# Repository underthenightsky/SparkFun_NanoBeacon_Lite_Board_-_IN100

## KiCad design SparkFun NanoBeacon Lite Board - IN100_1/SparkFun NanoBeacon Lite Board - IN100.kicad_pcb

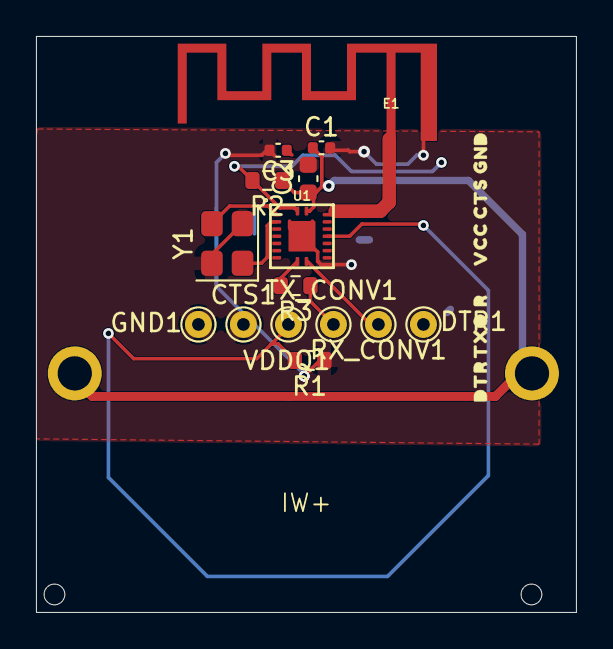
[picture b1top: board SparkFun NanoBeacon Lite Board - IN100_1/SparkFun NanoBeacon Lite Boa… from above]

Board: 2 copper layers, 30.0 x 32.0 mm, 16 parts (1 on the bottom side), 9 nets.

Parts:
BT1: Battery_Cell; BatteryHolder_Keystone_3009_1x2450
C1, C3: 0.1uF; C_0402_1005Metric
C2: 10uF; C_0603_1608Metric
CTS1: TestPoint; TestPoint_THTPad_D1.5mm_Drill0.7mm
DTR1: TestPoint; TestPoint_THTPad_D1.5mm_Drill0.7mm
E1: ANTENNA-GROUNDEDTRACE-15.2MM; TRACE_ANTENNA_2.4GHZ_15.2MM
GND1: TestPoint; TestPoint_THTPad_D1.5mm_Drill0.7mm
R1: 10k; R_0603_1608Metric
R2, R3: 1k; R_0603_1608Metric
RX_CONV1: TestPoint; TestPoint_THTPad_D1.5mm_Drill0.7mm
TX_CONV1: TestPoint; TestPoint_THTPad_D1.5mm_Drill0.7mm
U1: IN100
VDDQ1: TestPoint; TestPoint_THTPad_D1.5mm_Drill0.7mm
Y1: CRYSTAL-26MHZSMD-3.2X2.5; Crystal_SMD_3225-4Pin_3.2x2.5mm

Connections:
EN: C3.1, R2.2, U1.18 (EN)
GND: BT1.2 (-), C1.2, C2.2, C3.2, CTS1.1 (1_1), GND1.1 (1_1), R1.1, U1.19 (GND), Y1.2 (GND), Y1.4 (GND)
unnamed: R3.1, TX_CONV1.1 (1_1)
unnamed: R1.2, U1.13 (VDDQ), VDDQ1.1 (1_1)
unnamed: U1.1 (XO_N), Y1.3 (2)
unnamed: U1.2 (XO_P), Y1.1
RX/IO0: R3.2, U1.8 (RX/GPIO0)
TX/IO1: RX_CONV1.1 (1_1), U1.9 (TX/GPIO1)
VCC: BT1.1 (+), C1.1, C2.1, R2.1, U1.17 (VCC)

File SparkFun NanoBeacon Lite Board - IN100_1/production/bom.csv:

Designator,Footprint,Quantity,Value,LCSC Part #
BT1,BatteryHolder_Keystone_3009_1x2450,1,Battery_Cell,
"C1, C3",0402,2,0.1uF,
C2,0603,1,10uF,
"CTS1, DTR1, GND1, RX_CONV1, TX_CONV1, VDDQ1",TestPoint_THTPad_D1.5mm_Drill0.7mm,6,TestPoint,
E1,TRACE_ANTENNA_2.4GHZ_15.2MM,1,ANTENNA-GROUNDEDTRACE-15.2MM,
R1,0603,1,10k,
"R2, R3",0603,2,1k,
U1,IN100,1,IN100,
Y1,Crystal_SMD_3225-4Pin_3.2x2.5mm,1,CRYSTAL-26MHZSMD-3.2X2.5,

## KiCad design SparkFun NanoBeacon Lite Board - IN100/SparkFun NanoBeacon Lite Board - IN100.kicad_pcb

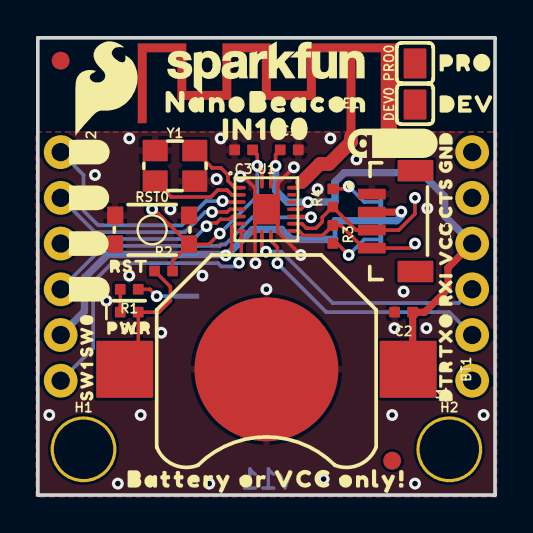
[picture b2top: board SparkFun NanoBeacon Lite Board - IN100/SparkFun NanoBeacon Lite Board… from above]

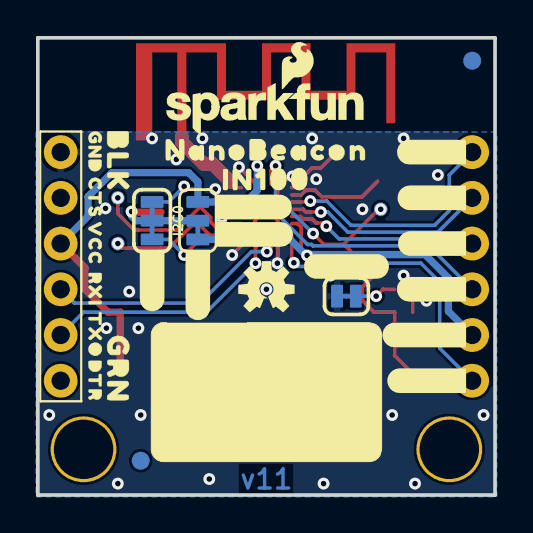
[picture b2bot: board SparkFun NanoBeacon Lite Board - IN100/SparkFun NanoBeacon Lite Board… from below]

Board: 2 copper layers, 25.4 x 25.4 mm, 63 parts (24 on the bottom side), 21 nets.

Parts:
BT1: BATTCON_12MM
BUS0: JUMPER-SMT_3_1-NC_TRACE_SILK; SMT-JUMPER_3_1-NC_TRACE_SILK
C1, C3: 0.1uF; 0402-TIGHT
C2: 10uF; 0402-TIGHT
D1: RED; LED-0402
DEV0: PROD_ID_PASTE_SILK; PRODUCT_IDENT_PASTE_SILK
E1: ANTENNA-GROUNDEDTRACE-15.2MM; TRACE_ANTENNA_2.4GHZ_15.2MM
FD1, FD2, FD3, FD4: FIDUCIAL1X2; FIDUCIAL-1X2
FRAME1: FRAME-LETTER; CREATIVE_COMMONS
H1, H2: STAND-OFF
I2C0: JUMPER-SMT_3_2-NC_TRACE_SILK; SMT-JUMPER_3_2-NC_TRACE_SILK
J1, J2: 1X06_NO_SILK
J3: Vertical Qwiic Connector; JST04_1MM_VERT
LOGO1: OSHW-LOGOS; OSHW-LOGO-S
LOGO2: SFE_LOGO_NAME_FLAME.1_INCH; SFE_LOGO_NAME_FLAME_.1
LOGO3: QWIIC_LOGO_5MM; QWIIC_5MM
PRO0: PROD_ID_PASTE_SILK; PRODUCT_IDENT_PASTE_SILK
PWR0: JUMPER-SMT_2_NC_TRACE_SILK; SMT-JUMPER_2_NC_TRACE_SILK
R1, R3, R4: 2.2k; 0402-TIGHT
R2: 1k; 0402-TIGHT
RST0: MOMENTARY-SWITCH-SPST-SMD-4.6X2.8MM; TACTILE_SWITCH_SMD_4.6X2.8MM
TP1, TP2, TP3: TEST-POINT3; PAD.03X.03
U1: IN100
U$1, U$29: NANOBEACON0
U$2: #_7#0
U$3: #_6#0
U$4: SFE_LOGO_NAME_.1
U$5, U$31: IN1000
U$6: #_5#0
U$7: #_4#0
U$8: SFE_LOGO_FLAME_.2
U$9: BATTERY_OR_VCC_ONLY##0
U$11: #I2C#0
U$12: #NOTES#0
U$13: #IO7_#0
U$14: #IO6_#0
U$15: #IO5_#0
U$16: #IO4_#0
U$17: #SW0_#0
U$18: #SW1_#0
U$19: #PWR#0
U$20: #SW0#3
U$21: SW00
U$22: SW10
U$23: RST0
U$24: #VCC#0
U$25: #BUS#0
U$26: PWR0
U$28: DEV0
U$30: PRO0
Y1: CRYSTAL-26MHZSMD-3.2X2.5; CRYSTAL-SMD-3.2X2.5MM

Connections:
EN: C3.1, R2.2, RST0.1, RST0.2, TP3.1, U1.18
GND: BT1.GND, C1.2, C2.2, C3.2, E1.GND, J1.6, J3.1, PWR0.1, RST0.3, RST0.4, U1.19, Y1.2, Y1.4
IO4: J2.4, U1.12
IO5: J2.3, U1.5
IO6: J2.2, U1.4
IO7: J2.1, U1.3
unnamed: U1.1, Y1.3
unnamed: U1.2, Y1.1
unnamed: PWR0.2, R1.1
unnamed: E1.ANT, U1.16
unnamed: D1.C, R1.2
unnamed: I2C0.1, R4.2
unnamed: BUS0.2, I2C0.2, J3.2
unnamed: I2C0.3, R3.2
RX/IO0: J1.3, U1.8
SCL/IO2: J3.4, R3.1, TP2.1, U1.10
SDA/IO3: J3.3, R4.1, TP1.1, U1.11
SW0: BUS0.3, J2.5, U1.6
SW1: J2.6, U1.7
TX/IO1: J1.2, U1.9
VCC: BT1.PWR@1, BT1.PWR@2, BUS0.1, C1.1, C2.1, D1.A, J1.4, R2.1, U1.13, U1.17

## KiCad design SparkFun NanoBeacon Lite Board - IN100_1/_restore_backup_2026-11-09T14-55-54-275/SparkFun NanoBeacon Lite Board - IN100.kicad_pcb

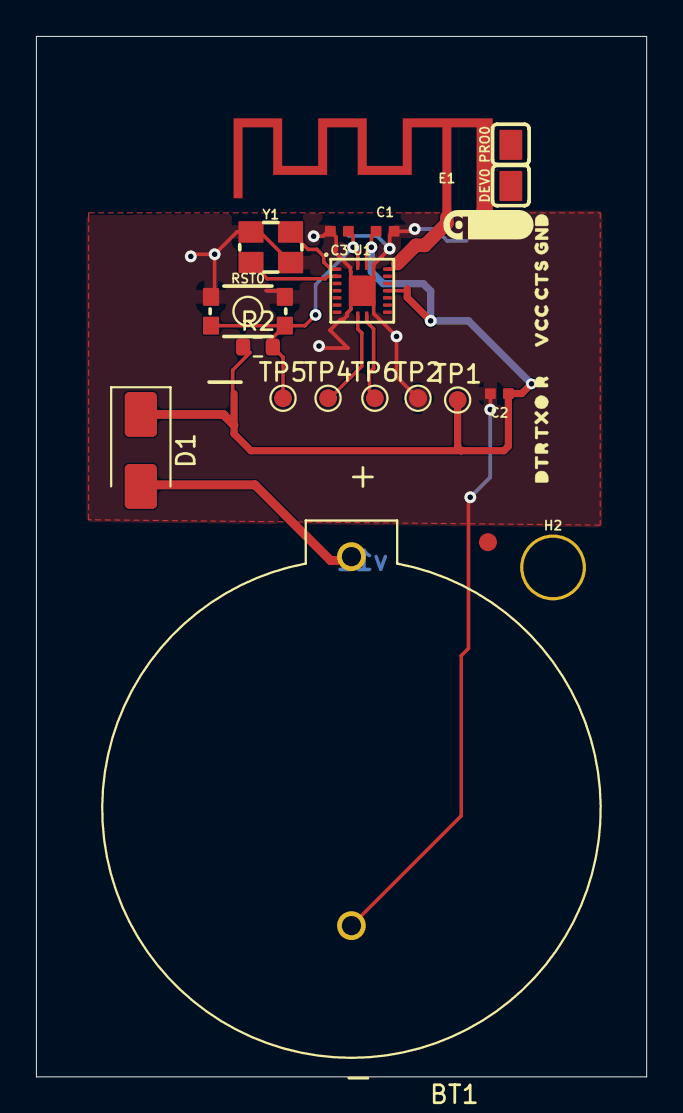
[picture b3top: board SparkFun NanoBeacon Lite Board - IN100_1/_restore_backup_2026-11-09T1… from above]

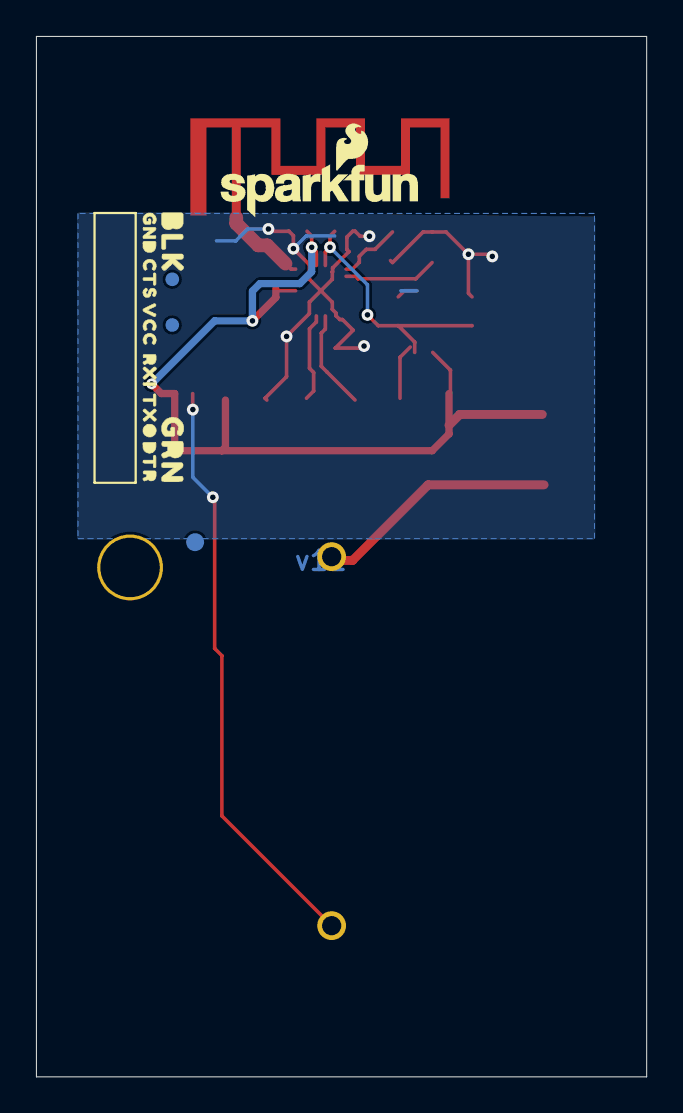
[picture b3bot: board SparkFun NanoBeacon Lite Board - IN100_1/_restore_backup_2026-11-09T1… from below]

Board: 2 copper layers, 33.9 x 57.8 mm, 25 parts (4 on the bottom side), 8 nets.

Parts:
BT1: BATTERY-12MM_SMD; BAT_BH1000G
C1, C3: 0.1uF; 0402-TIGHT
C2: 10uF; 0402-TIGHT
D1: D_Schottky; D_SMA
DEV0: PROD_ID_PASTE_SILK; PRODUCT_IDENT_PASTE_SILK
E1: ANTENNA-GROUNDEDTRACE-15.2MM; TRACE_ANTENNA_2.4GHZ_15.2MM
FD3, FD4: FIDUCIAL1X2; FIDUCIAL-1X2
FRAME1: FRAME-LETTER; CREATIVE_COMMONS
H2: STAND-OFF
LOGO2: SFE_LOGO_NAME_FLAME.1_INCH; SFE_LOGO_NAME_FLAME_.1
LOGO3: QWIIC_LOGO_5MM; QWIIC_5MM
PRO0: PROD_ID_PASTE_SILK; PRODUCT_IDENT_PASTE_SILK
R2: 1k; R_0603_1608Metric
RST0: MOMENTARY-SWITCH-SPST-SMD-4.6X2.8MM; TACTILE_SWITCH_SMD_4.6X2.8MM
TP1, TP2, TP4, TP5, TP6: TestPoint; TestPoint_Pad_D1.0mm
TP1#2, TP2#2: TEST-POINT3; PAD.03X.03
U1: IN100
Y1: CRYSTAL-26MHZSMD-3.2X2.5; CRYSTAL-SMD-3.2X2.5MM

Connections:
EN: C3.1, R2.2, RST0.1, RST0.2 (1), TP5.1 (1_1), U1.18 (EN)
GND: C1.2, C2.2, C3.2, E1.GND, RST0.3 (2), RST0.4 (2), TP2.1 (1_1), U1.19 (GND), Y1.2 (GND), Y1.4 (GND)
unnamed: E1.ANT (SIGNAL), U1.16 (RF_TX)
unnamed: U1.1 (XO_N), Y1.3 (2)
unnamed: U1.2 (XO_P), Y1.1
RX/IO0: TP4.1 (1_1), U1.8 (RX/GPIO0)
TX/IO1: TP6.1 (1_1), U1.9 (TX/GPIO1)
VCC: C1.1, C2.1, D1.1 (K), R2.1, TP1.1 (1_1), U1.13 (VDDQ), U1.17 (VCC)

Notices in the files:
parts and their libraries:
Released under the Creative Commons Attribution Share-Alike 4.0 License
https://creativecommons.org/licenses/by-sa/4.0
